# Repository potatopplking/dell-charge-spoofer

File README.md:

# Yet another Dell charge spoofer

Spoofer emulates genuine Dell laptop charger, allowing you to charge your laptop with any power source (with correct voltage and current rating). Built using ATTiny13. This spoofer is very simple, containing only 2 ICs and a few resistors and capacitors.

## Motivation

If you need to use your Dell laptop with non-original charger (or any generic power source), you need to emulate communication between laptop and charger. This communication takes place on 1-wire bus (center pin of laptop power in connector).

## Usage

### Prerequisities

On the software side, you'll need `avr-gcc`, `avr-libc` and `avrdude`. For the hardware you'll need some AVR programmer and a spoofer (it's easy to build one yourself!).

### Compile & flash

```
make compile
make fuse # set AVR fuses (config bits)
make flash
```

### Connect

See schematic. Connect GND and output voltage of your source to voltage input of spoofer. Connect center pin of the laptop connector to DATA pin of spoofer. GND should go on the outer shield of connector, voltage should be connected to inner shield of connector.

*Important: spoofer doesn't regulate or monitor voltage of the power source - it's up to you to check that voltage matches original charger!*

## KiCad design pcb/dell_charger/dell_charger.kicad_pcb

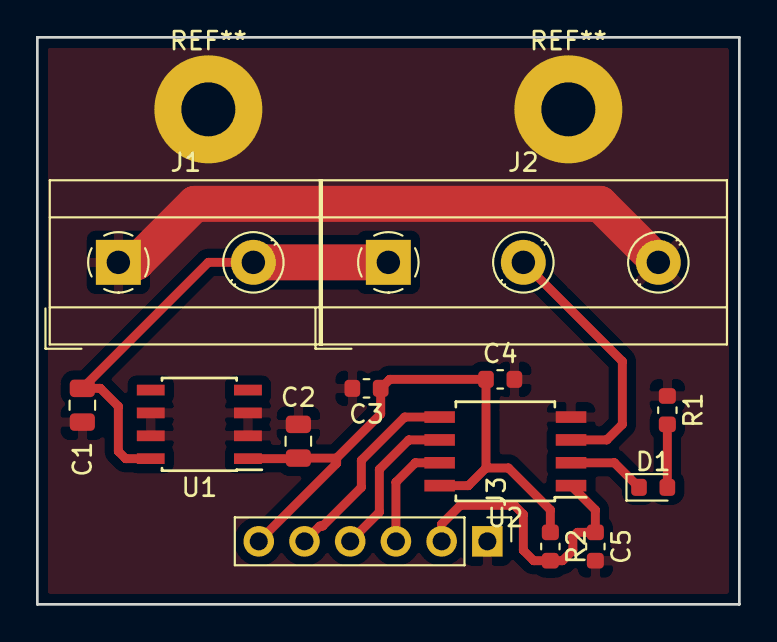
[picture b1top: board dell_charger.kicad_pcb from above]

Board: 2 copper layers, 39.0 x 31.5 mm, 13 parts (0 on the bottom side), 10 nets.

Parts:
C1, C2: 10u; C_0805_2012Metric
C3: 1u; C_0603_1608Metric
C4, C5: 100n; C_0603_1608Metric
D1: LED; LED_0603_1608Metric
J1: Input terminal; TerminalBlock_MetzConnect_Type171_RT13702HBWC_1x02_P7.50mm_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
J2: Output terminal; TerminalBlock_MetzConnect_Type171_RT13703HBWC_1x03_P7.50mm_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
J3: Programmer; PinHeader_1x06_P2.54mm_Vertical
R1: 470; R_0603_1608Metric
R2: 4k7; R_0603_1608Metric
U1: L78L05_SO8; SOIC-8_3.9x4.9mm_P1.27mm
U2: ATtiny13-20SU; SOIJ-8_5.3x5.3mm_P1.27mm

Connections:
+5V: C2.1, C3.1, C4.1, J3.6, R2.1, U1.1, U2.8
/DATA: J2.2, U2.3
/LED: D1.1, U2.2
/MISO: J3.4, U2.6
/MOSI: J3.5, U2.5
/SCK: J3.3, U2.7
GND: C1.2, C2.2, C3.2, C4.2, C5.2, J1.1, J2.3, J3.1, R1.1, U1.2, U1.3, U1.6, U1.7, U2.4
unnamed: C1.1, J1.2, J2.1, U1.8
unnamed: C5.1, J3.2, R2.2, U2.1
unnamed: D1.2, R1.2

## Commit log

2021-12-27 Added src files
2021-12-27 Fixed typo
